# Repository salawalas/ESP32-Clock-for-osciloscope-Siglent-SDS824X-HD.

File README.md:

# Zegar RTC dla Siglent SDS800X HD (ESP32 + DS3231 + W5500)

Pudełko, które po włączeniu wysyła do oscyloskopu aktualną datę i godzinę (SCPI po TCP, port 5025).
Czas pochodzi z DS3231 (działa bez sieci), a gdy w zasięgu jest skonfigurowane Wi-Fi, jest odświeżany z NTP.

## Połączenia (ESP32 DevKit C)

| Moduł  | Pin modułu | GPIO ESP32 |
|--------|-----------|-----------|
| DS3231 | SDA / SCL | 21 / 22   |
| W5500  | SCLK      | 18        |
|        | MISO      | 19        |
|        | MOSI      | 23        |
|        | SCS       | 5         |
|        | INT       | 4         |
|        | RST       | 16        |
| oba    | zasilanie, GND | 3V3 (lub 5V wg opisu na module W5500 - tylko jedno z nich), GND |

Piny zmienisz w `main/pins.h`. Kabel Ethernet idzie prosto z W5500 do portu LAN oscyloskopu.
Przycisk BOOT na płytce = "wyślij czas do oscyloskopu teraz".

## Ustawienia w oscyloskopie

LAN: stały adres IP `192.168.77.2`, maska `255.255.255.0`, brama pusta. Wyłącz w menu daty/czasu
synchronizację NTP przy starcie, żeby nie nadpisywała czasu z pudełka.

## Budowanie

ESP-IDF >= 5.3 (testowane tylko na papierze, patrz uwaga na końcu):

    idf.py set-target esp32
    idf.py build flash monitor

Sterownik W5500:
- IDF 5.3-5.5: wbudowany; `sdkconfig.defaults` go włącza (menuconfig -> Component config -> Ethernet -> SPI Ethernet -> W5500).
- IDF >= 6.0: sterownik jest osobnym komponentem `espressif/w5500`; pobiera go menedżer komponentów
  na podstawie `main/idf_component.yml` (przy pierwszym buildzie potrzebny internet).

PlatformIO: w `platformio.ini` jest `src_dir = main`, więc nic nie trzeba przenosić.

## Konfiguracja (konsola szeregowa, 115200)

Ustawienia trafiają do NVS i przetrwają restart. Przykład:

    set wifi_ssid MojaSiec
    set wifi_pass tajnehaslo
    set wifi_ip 192.168.1.50
    set wifi_mask 255.255.255.0
    set wifi_gw 192.168.1.1
    set wifi_dns 192.168.1.1
    set ntp_server pool.ntp.org
    set tz CET-1CEST,M3.5.0,M10.5.0/3
    sync

Inne komendy: `show`, `time`, `settime RRRR-MM-DD GG:MM:SS` (czas lokalny), `push`, `scope <SCPI>`,
`factory`, `reboot`. Wartości ze spacjami podawaj w cudzysłowie.

## Format komend SCPI

Zgodnie z Programming Guide (SDS800X HD) oscyloskop przyjmuje datę i czas jako liczby bez separatorów:
`:SYSTem:DATE 20191220` (RRRRMMDD) i `:SYSTem:TIME 081040` (GGMMSS). Domyślne wzorce w firmware
(`scope_date_fmt`, `scope_time_fmt`) to odpowiednio `:SYSTem:DATE %Y%m%d` i `:SYSTem:TIME %H%M%S`.
Wzorce są w formacie `strftime` i zmienisz je bez rekompilacji, np. `set scope_date_fmt "..."`.
Odczyt kontrolny: `scope :SYSTem:DATE?` i `scope :SYSTem:TIME?`; po każdej wysyłce widać go też w logu.

## Zachowanie

- Start: czas z DS3231 -> zegar systemowy -> wysyłka do oscyloskopu (ponawiana co 3 s przez 10 min,
  bo oscyloskop startuje wolniej niż ESP32).
- Jeśli `wifi_ssid` jest ustawione i `wifi_boot` = 1: równolegle próba Wi-Fi + NTP; po sukcesie czas jest
  zapisywany do DS3231 (UTC) i wysyłany do oscyloskopu ponownie, a Wi-Fi jest wyłączane.
- W terenie, przy zasilaniu z USB oscyloskopu, rozważ `set wifi_boot 0` (mniejszy pobór prądu).
- Każde podniesienie linku Ethernet (np. restart oscyloskopu przy zasilaniu pudełka z powerbanku) wywołuje
  ponowną wysyłkę czasu; przycisk BOOT nadal działa jako ręczne wymuszenie.
- `scope_resync` (minuty) włącza okresowe ponawianie wysyłki, domyślnie 0.

Uwaga: konwersja daty (`timeutil.h`) była testowana na PC; reszta - na sprzęcie przez użytkownika, w toku.

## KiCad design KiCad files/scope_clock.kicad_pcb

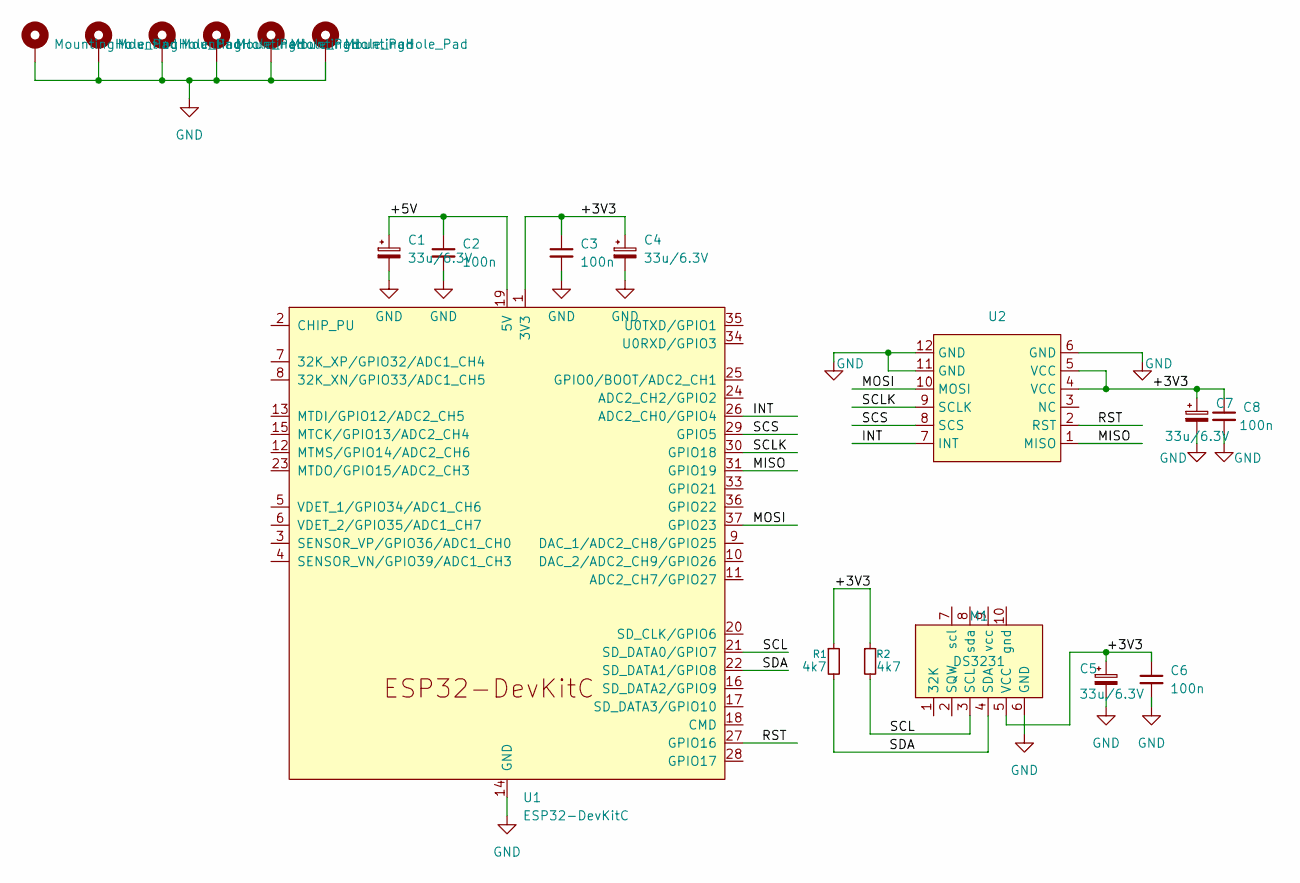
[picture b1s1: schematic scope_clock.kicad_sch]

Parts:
C1, C4, C5, C7: 33u/6.3V; CP_Radial_Tantal_D4.5mm_P5.00mm
C2, C3, C6, C8: 100n; C_0805_2012Metric_Pad1.18x1.45mm_HandSolder
H1, H2, H3, H4, H5, H6: MountingHole_Pad; MountingHole_2.5mm_Pad_TopBottom
M1: DS3231; DS3231_module_H
R1, R2: 4k7; R_0805_2012Metric_Pad1.20x1.40mm_HandSolder
U1: ESP32-DevKitC; ESP32-DevKitC-USB-C_MOD
U2: W5500_module_Mini

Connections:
/+3V3: C3.1, C4.1, C5.1, C6.1, C7.1, C8.1, M1.5 (VCC), R1.1, R2.1, U1.1 (3V3), U2.4 (VCC), U2.5 (VCC)
/+5V: C1.1, C2.1, U1.19 (5V)
/INT: U1.26 (ADC2_CH0/GPIO4), U2.7 (INT)
/MISO: U1.31 (GPIO19), U2.1 (MISO)
/MOSI: U1.37 (GPIO23), U2.10 (MOSI)
/RST: U1.27 (GPIO16), U2.2 (RST)
/SCL: M1.3 (SCL), R2.2, U1.21 (SD_DATA0/GPIO7)
/SCLK: U1.30 (GPIO18), U2.9 (SCLK)
/SCS: U1.29 (GPIO5), U2.8 (SCS)
/SDA: M1.4 (SDA), R1.2, U1.22 (SD_DATA1/GPIO8)
GND: C1.2, C2.2, C3.2, C4.2, C5.2, C6.2, C7.2, C8.2, H1.1 (1_1), H2.1 (1_1), H3.1 (1_1), H4.1 (1_1), H5.1 (1_1), H6.1 (1_1), M1.6 (GND), U1.14 (GND), U1.32 (GND), U1.38 (GND), U2.6 (GND), U2.11 (GND), U2.12 (GND)

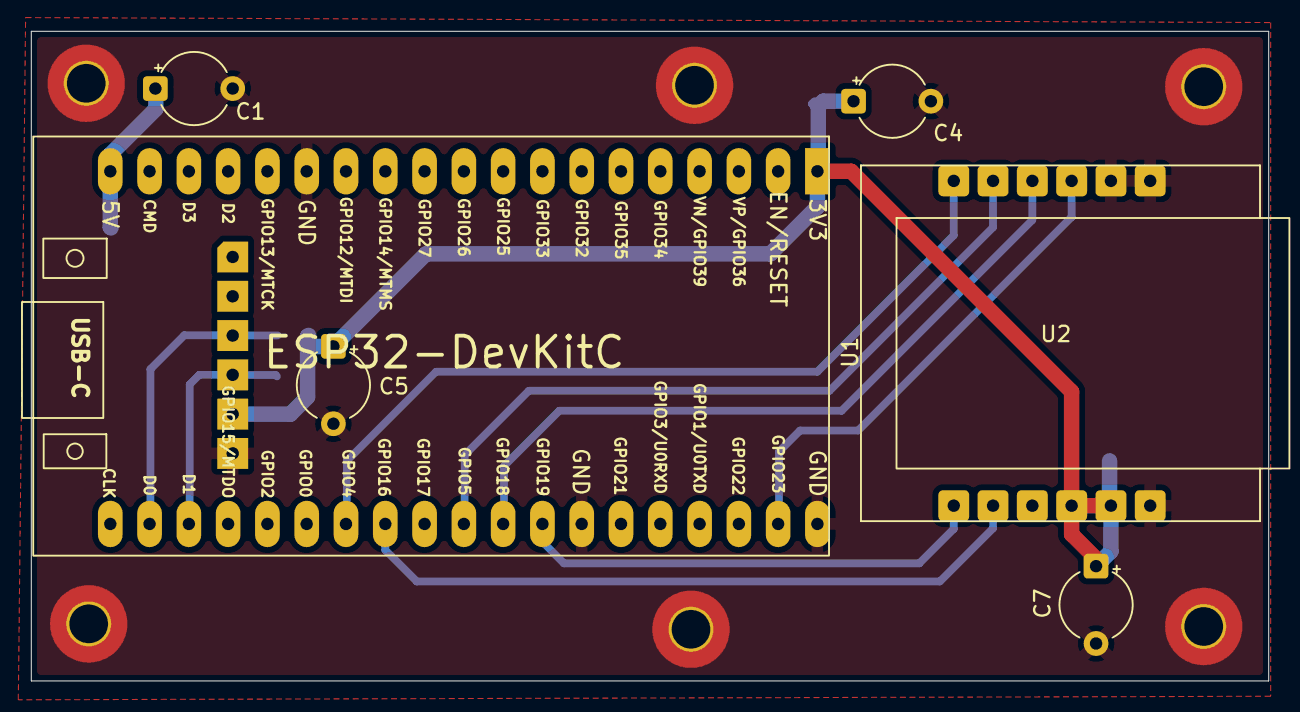
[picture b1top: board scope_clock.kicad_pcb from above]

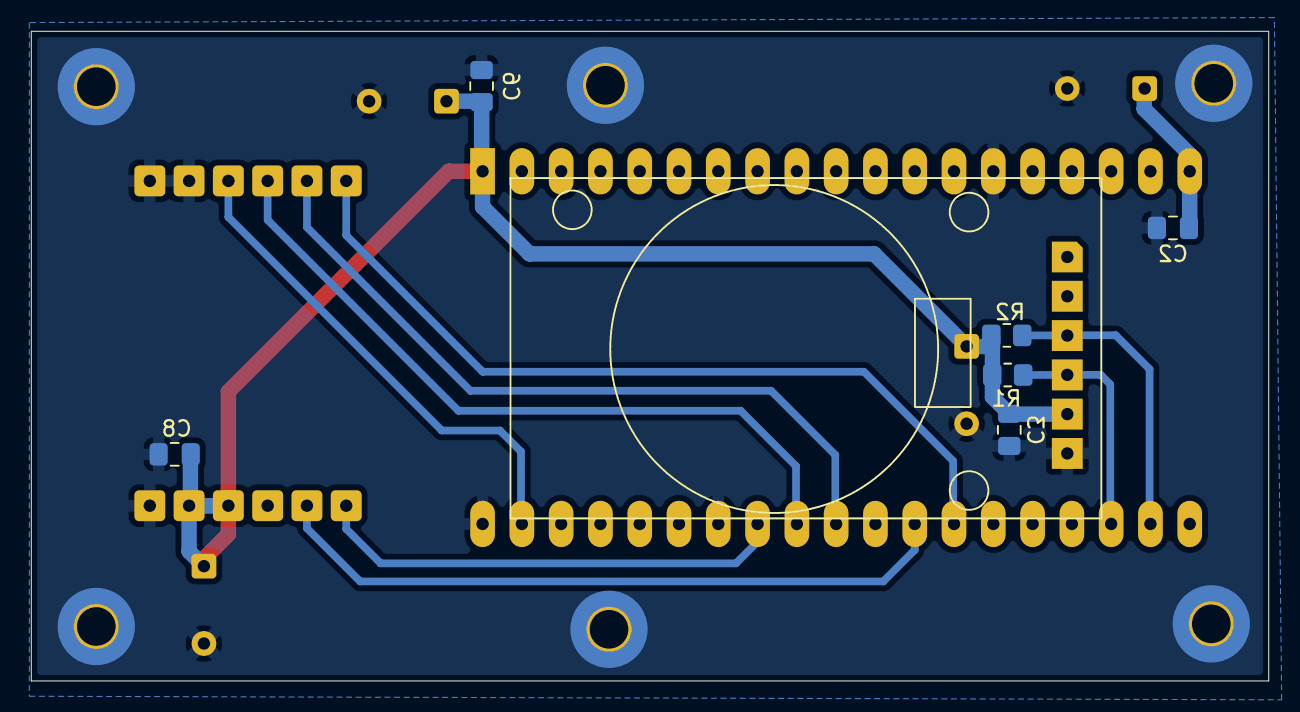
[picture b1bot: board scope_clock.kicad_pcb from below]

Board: 2 copper layers, 80.0 x 42.0 mm, 19 parts (7 on the bottom side), 11 nets.
